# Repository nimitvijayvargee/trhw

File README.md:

# this ruler has wifi
(And bluetooth!)

This is an RP2040 ruler that implements wifi, bluetooth, BLE along with a 4MB Flash storage, LEDs, Input buttons and some cool units and lengths!

## Feature list
- wifi
- bluetooth (BT5.2 & BLE)
- 4x RGB Addressable LEDs
- 3x Input buttons
- GPIO output header for more hacky
- Weird units
  - Space Units like Light-picosecond, 10e-18 parsecs and 10e-12 AU
  - The actual wavelength (and quarter wave!) of Bluetooth and Wifi (2.4GHz and - 5GHz)!
- Useful units
  - Inches (down to 0.02 inches!)
  - mm 
  - M2, M2.5 and M3 Diameter holes
  - Length Unit conversion chart
- 4MB QSPI Flash
- Buck-Boost Conversion
- Battery charging and reverse voltage protection.
  - No overcurrent, short circuit or overheating protection!

## Schematic 

## PCB

The production files for JLCPCB are included in `PCB/production`

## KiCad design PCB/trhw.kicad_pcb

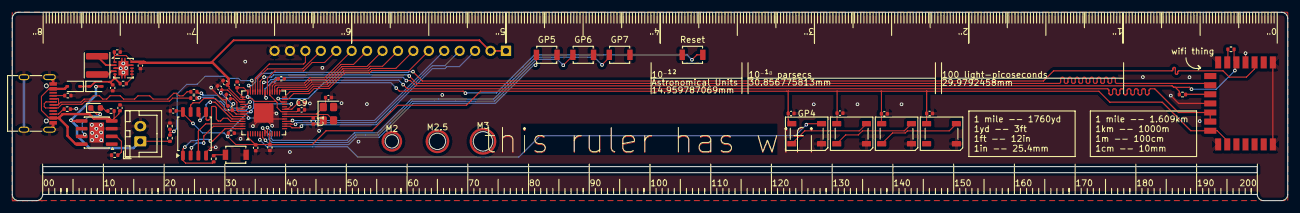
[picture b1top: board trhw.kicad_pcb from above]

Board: 2 copper layers, 210.0 x 31.0 mm, 56 parts (0 on the bottom side), 54 nets.

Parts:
C1, C2: 15pf; C_0402_1005Metric
C3, C4, C5, C6, C7, C8, C9, C10, C11, C14, C19, C20, C21, C22: 100n; C_0402_1005Metric
C12, C13: 1u; C_0402_1005Metric
C15, C16, C17, C18: 10u; C_0402_1005Metric
D1, D2: BAT60A; D_SOD-323
D3: LED; LED_0603_1608Metric
D4, D5, D6, D7: WS2812B; LED_WS2812B_PLCC4_5.0x5.0mm_P3.2mm
GP5, GP6, GP7: SW_Push; SW_SPST_B3U-1000P
J1: USB_C_Receptacle_USB2.0_14P; USB_C_Receptacle_G-Switch_GT-USB-7010ASV
J2: Conn_01x02; JST_XH_B2B-XH-A_1x02_P2.50mm_Vertical
J4: Conn_01x16; PinSocket_1x16_P2.54mm_Vertical
L1: 2.2uH; L_Sunlord_SWPA4020S
R1, R2: 5.1k; R_0402_1005Metric
R3: 100; R_0402_1005Metric
R4, R10: 1k; R_0402_1005Metric
R5: 470; R_0402_1005Metric
R6: 10k; R_0402_1005Metric
R7: 2k; R_0402_1005Metric
R8: 100k; R_0402_1005Metric
R9: 200k; R_0402_1005Metric
R11, R12: 30; R_0402_1005Metric
Reset: SW_Push; SW_SPST_B3U-1000P
SW1: SW_Push; SW_SPST_B3U-1000P
U1: RP2040; QFN-56-1EP_7x7mm_P0.4mm_EP3.2x3.2mm
U2: W25Q32JVSS; SOIC-8_5.3x5.3mm_P1.27mm
U3: TPS63001; Texas_DRC0010J_ThermalVias
U4: Raspberry Pi Radio Module 2; rpi_rmc20452t
U5: TP4056-42-ESOP8; SOIC-8-1EP_3.9x4.9mm_P1.27mm_EP2.41x3.3mm_ThermalVias
Y1: Crystal_GND24; Crystal_SMD_Abracon_ABM8G-4Pin_3.2x2.5mm

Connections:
+1V1: C3.1, C4.1, C12.1, U1.23 (DVDD), U1.45 (VREG_VOUT), U1.50 (DVDD)
+3V3: C5.1, C6.1, C7.1, C8.1, C9.1, C10.1, C11.1, C13.1, C14.1, C16.1, C17.1, C19.1, C20.1, C21.1, C22.1, D4.1 (VDD), D5.1 (VDD), D6.1 (VDD), D7.1 (VDD), J4.1, J4.2, U1.1 (IOVDD), U1.10 (IOVDD), U1.22 (IOVDD), U1.33 (IOVDD), U1.42 (IOVDD), U1.43 (ADC_AVDD), U1.44 (VREG_IN), U1.48 (USB_VDD), U1.49 (IOVDD), U2.8 (VCC), U3.1 (VOUT), U3.10 (FB), U4.14 (VDDIO), U4.16 (VIN)
+BATT: D2.2 (A), J2.1, R8.1, U5.5 (BAT)
Boot: R4.1, U1.56 (QSPI_SS), U2.1 (~CS)
GND: C1.2, C2.2, C3.2, C4.2, C5.2, C6.2, C7.2, C8.2, C9.2, C10.2, C11.2, C12.2, C13.2, C14.2, C15.2, C16.2, C17.2, C18.2, C19.2, C20.2, C21.2, C22.2, D4.3 (VSS), D5.3 (VSS), D6.3 (VSS), D7.3 (VSS), GP5.2, GP6.2, GP7.2, J1.A1 (GND), J1.A12 (GND), J1.B1 (GND), J1.B12 (GND), J1.S1 (SHIELD), J2.2, J4.15, J4.16, R1.2, R2.2, R7.2, R9.2, Reset.1, SW1.2, U1.19 (TESTEN), U1.57 (GND), U2.4 (GND), U3.3 (PGND), U3.9 (GND), U3.11 (PGND), U4.1 (GND), U4.4 (GND), U4.7 (GND), U4.11 (GND), U4.15 (GND), U4.21 (GND), U5.3 (GND), U5.9 (EPAD), Y1.2, Y1.4
GP4: D4.4 (DIN), U1.6 (GPIO4)
GP5: GP5.1, U1.7 (GPIO5)
GP6: GP6.1, U1.8 (GPIO6)
GP7: GP7.1, U1.9 (GPIO7)
GP13: J4.3, U1.16 (GPIO13)
GP14: J4.4, U1.17 (GPIO14)
GP15: J4.5, U1.18 (GPIO15)
GP16: J4.6, U1.27 (GPIO16)
GP17: J4.7, U1.28 (GPIO17)
GP18: J4.8, U1.29 (GPIO18)
GP19: J4.9, U1.30 (GPIO19)
GP20: J4.10, U1.31 (GPIO20)
GP21: J4.11, U1.32 (GPIO21)
GP22: J4.12, U1.34 (GPIO22)
GP23: U1.35 (GPIO23), U4.12 (WL_ON), U4.13 (BT_ON)
GP24: R5.1, R6.1, U1.36 (GPIO24), U4.5 (DI)
GP25: U1.37 (GPIO25), U4.9 (CS)
GP26: J4.13, U1.38 (GPIO26_ADC0)
GP27: J4.14, U1.39 (GPIO27_ADC1)
GP28: R8.2, R9.1, U1.40 (GPIO28_ADC2)
GP29: U1.41 (GPIO29_ADC3), U4.3 (SCLK)
unnamed: D3.2 (A), R10.2
unnamed: D3.1 (K), U5.7 (~CHRG)
unnamed: D4.2 (DOUT), D5.4 (DIN)
unnamed: D5.2 (DOUT), D6.4 (DIN)
unnamed: D6.2 (DOUT), D7.4 (DIN)
unnamed: J1.A5 (CC1), R1.1
unnamed: J1.B5 (CC2), R2.1
unnamed: R4.2, SW1.1
unnamed: U1.52 (QSPI_SCLK), U2.6 (CLK)
unnamed: U1.53 (QSPI_SD0), U2.5 (DI/IO_{0})
unnamed: U1.55 (QSPI_SD1), U2.2 (DO/IO_{1})
unnamed: U1.54 (QSPI_SD2), U2.3 (~WP/IO_{2})
unnamed: U1.51 (QSPI_SD3), U2.7 (~HOLD/~RESET/IO_{3})
unnamed: Reset.2, U1.26 (RUN)
unnamed: R12.2, U1.46 (USB_DM)
unnamed: R11.2, U1.47 (USB_DP)
unnamed: C1.1, U1.20 (XIN), Y1.3
unnamed: C2.1, U1.21 (XOUT), Y1.1
unnamed: R3.2, U3.6 (EN), U3.7 (PS/SYNC), U3.8 (VINA)
unnamed: L1.2, U3.4 (L1)
unnamed: L1.1, U3.2 (L2)
unnamed: R5.2, U4.6 (DO)
unnamed: R6.2, U4.10 (nIRQ)
unnamed: R7.1, U5.2 (PROG)
USB_D+: J1.A6 (D+), J1.B6 (D+), R11.1
USB_D-: J1.A7 (D-), J1.B7 (D-), R12.1
VBUS: C18.1, D1.2 (A), J1.A4 (VBUS), J1.A9 (VBUS), J1.B4 (VBUS), J1.B9 (VBUS), R10.1, U5.4 (V_{CC}), U5.8 (CE)
VCC: C15.1, D1.1 (K), D2.1 (K), R3.1, U3.5 (VIN)

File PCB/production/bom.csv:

Designator,Footprint,Quantity,Value,LCSC Part #
"C1, C2",0402,2,15pf,
"C10, C11, C14, C19, C20, C21, C22, C3, C4, C5, C6, C7, C8, C9",0402,14,100n,
"C12, C13",0402,2,1u,
"C15, C16, C17, C18",0402,4,10u,
"D1, D2",D_SOD-323,2,BAT60A,
D3,0603,1,LED,
"D4, D5, D6, D7",LED_WS2812B_PLCC4_5.0x5.0mm_P3.2mm,4,WS2812B,
"GP5, GP6, GP7, RESET, SW1",SW_SPST_B3U-1000P,5,SW_Push,
J1,USB_C_Receptacle_G-Switch_GT-USB-7010ASV,1,USB_C_Receptacle_USB2.0_14P,
J2,JST_XH_B2B-XH-A_1x02_P2.50mm_Vertical,1,Conn_01x02,
J4,PinSocket_1x16_P2.54mm_Vertical,1,Conn_01x16,
L1,L_Sunlord_SWPA4020S,1,2.2uH,
"R1, R2",0402,2,5.1k,
"R10, R4",0402,2,1k,
"R11, R12",0402,2,30,
R3,0402,1,100,
R5,0402,1,470,
R6,0402,1,10k,
R7,0402,1,2k,
R8,0402,1,100k,
R9,0402,1,200k,
U1,QFN-56-1EP_7x7mm_P0.4mm_EP3.2x3.2mm,1,RP2040,
U2,SOIC-8_5.3x5.3mm_P1.27mm,1,W25Q32JVSS,
U3,Texas_DRC0010J_ThermalVias,1,TPS63001,
U4,rpi_rmc20452t,1,Raspberry Pi Radio Module 2,
U5,SOIC-8-1EP_3.9x4.9mm_P1.27mm_EP2.41x3.3mm_ThermalVias,1,TP4056-42-ESOP8,
Y1,Crystal_SMD_Abracon_ABM8G-4Pin_3.2x2.5mm,1,Crystal_GND24,

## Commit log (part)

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2026-06-07 stuff
2026-06-07 stuff 2
2026-06-08 fix journal
2026-06-08 fix PCB lock files
2026-06-12 Final
2026-06-12 Thermal via fix
2026-06-12 Production Files
